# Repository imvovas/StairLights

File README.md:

# StairLights
Програмно-аппаратный комплект StairLights

Код для управления Arduino Leonardo (китайский клон)

В коде прошивки добавлены:
* управление скоростью отработки эффектов через подстроечный резистор;
* удалена поддержка кнопок вместе с библиотекой подавления дребезга;
* исправлены ошибки в визуальных эффектах.

Аппаратная часть находится в папке /Board. Актуальная версия платы в архиве StairLights_clips_2020-08-26.zip.
В актуальной редакции платы добавлены:
* дополнительные выводы 12 Вольт, 5 Вольт;
* добавлено два входа для сенсоров;
* добавлены отладочные светодиоды.
* Плата переведена на двухсторонний монтаж и под фабричное изготовление.

Ограничения:
- Напряжение питания устройства - 12 Вольт.
- Для питания Arduino Leonardo (китайский клон) использован DC-DC преобразователь (7-24 Вольта - 5 Вольт).
- Управляющие выходы подключаются к 8 сегментам LED-ленты 12 Вольт и потребляемой мощностью не более 500 мА на один сегмент.
- Используются управляющие сигналы TTL-уровня, при отсутствии сигнала входы притянуты к "земле".
- В качестве сенсоров можно использовать любые датчики/выключатели при условия соблюдения TTL-уровней сигнала. В коде прошивки реализована логика с поддержкой двух входов из четырех.

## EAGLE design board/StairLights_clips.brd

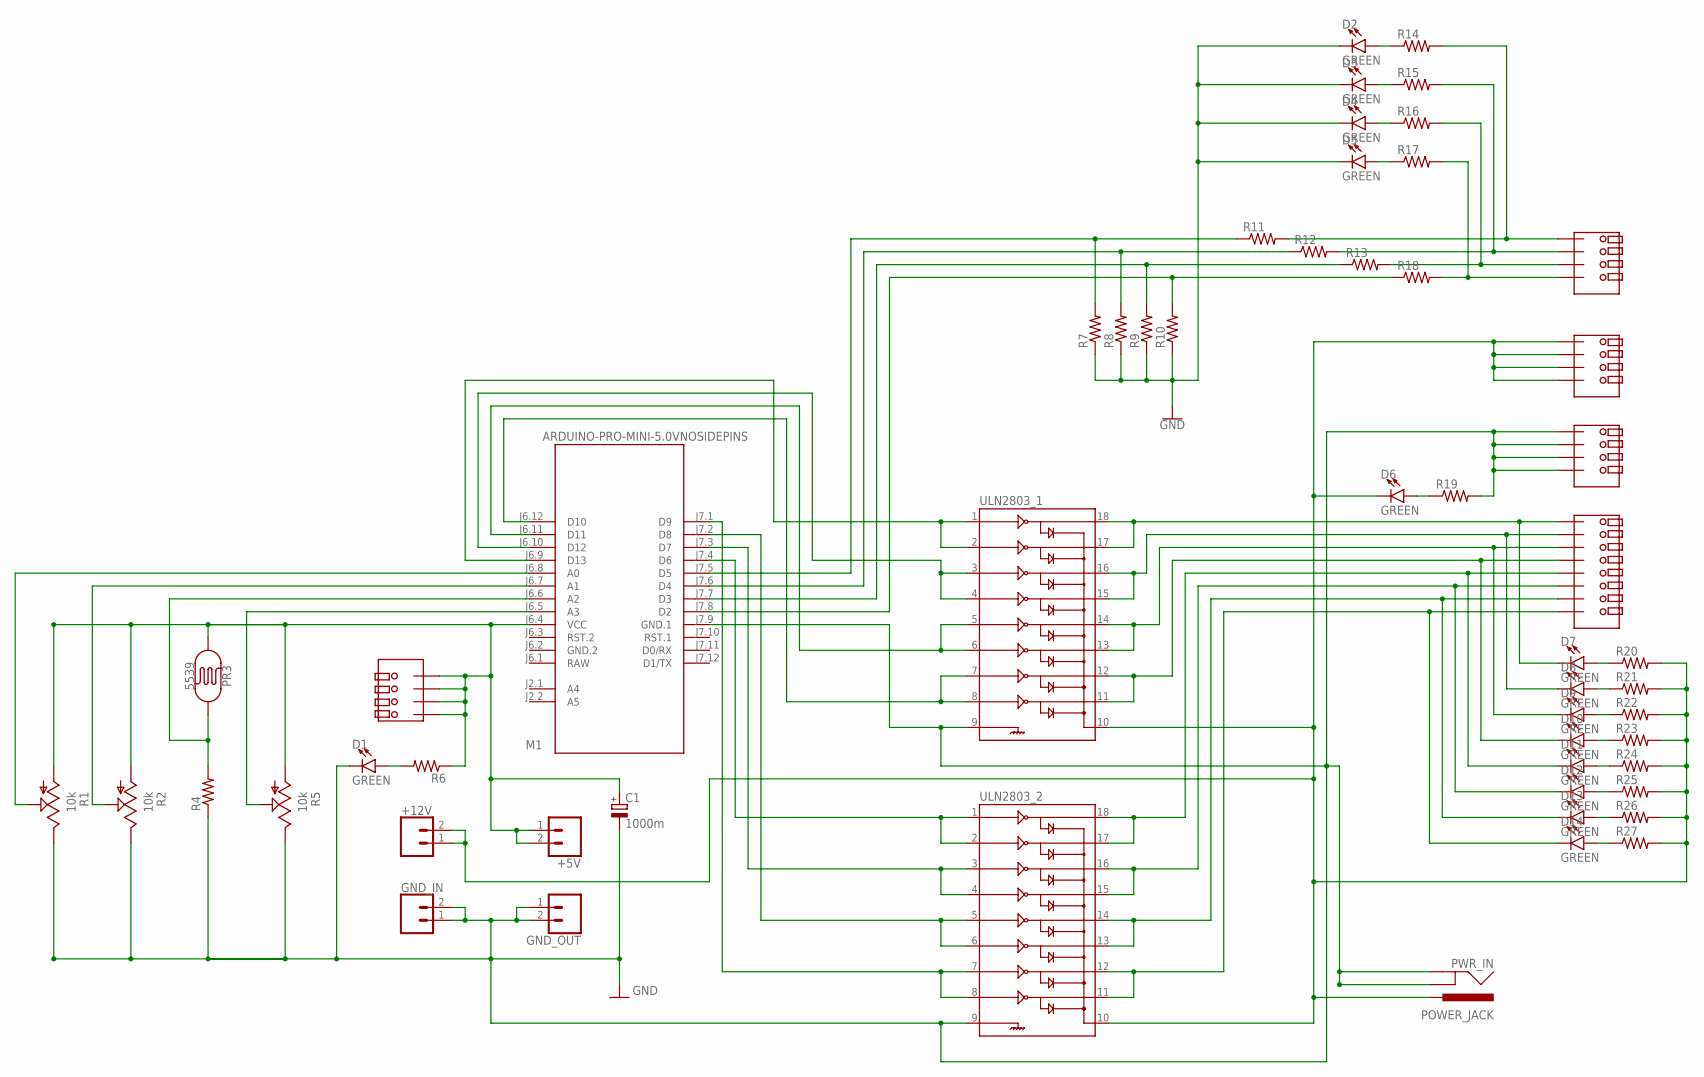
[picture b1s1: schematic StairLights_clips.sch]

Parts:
+5V, +12V: CONN_02; 1X02
C1: 1000m; E5-5
D1, D2, D3, D4, D5, D6, D7, D8, D9, D10, D11, D12, D13, D14: GREEN; LED-1206
GND_IN: CONN_02; 1X02
GND_OUT: CONN_02; 1X02
M1: ARDUINO-PRO-MINI-5.0VNOSIDEPINS; ARDUINO-PRO-MINI
PR3: 5539; PHOTOCELL
PWR_IN: POWER_JACK; POWER_JACK_PTH
R1, R2, R5: 10k; S64W
R4, R7, R8, R9, R10: 10k; R0805
R6, R11, R12, R13, R14, R15, R16, R17, R18, R19, R20, R21, R22, R23, R24, R25, R26, R27: 330; R0805
SC1, SC2, SC3, SC4: KF141V-4
SC5: KF141V-8
ULN2803_1, ULN2803_2: ULN2803DIP; DIL18

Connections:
GND: C1.-, D1.C, D2.C, D3.C, D4.C, D5.C, GND_IN.1, GND_IN.2, GND_OUT.1, GND_OUT.2, M1.J7.9 (GND.1), PWR_IN.GND, PWR_IN.GNDBREAK, R1.E, R2.E, R4.1, R5.E, R7.1, R8.1, R9.1, R10.1, R19.2, SC4.P$1, SC4.P$2, SC4.P$3, SC4.P$4, SC4.P$9, SC4.P$10, SC4.P$11, SC4.P$12, ULN2803_1.9, ULN2803_2.9
GND.2: M1.J6.2 (GND.2)
unnamed: D7.C, SC5.P$1, SC5.P$9, ULN2803_1.17, ULN2803_1.18
unnamed: D8.C, SC5.P$2, SC5.P$10, ULN2803_1.15, ULN2803_1.16
unnamed: M1.J7.7 (D3), R9.2, R13.1
unnamed: D9.C, SC5.P$3, SC5.P$11, ULN2803_1.13, ULN2803_1.14
unnamed: M1.J6.12 (D10), ULN2803_1.7, ULN2803_1.8
unnamed: D10.C, SC5.P$4, SC5.P$12, ULN2803_1.11, ULN2803_1.12
unnamed: M1.J6.6 (A2), PR3.2, R4.2
unnamed: D11.C, SC5.P$5, SC5.P$13, ULN2803_2.17, ULN2803_2.18
unnamed: D12.C, SC5.P$6, SC5.P$14, ULN2803_2.15, ULN2803_2.16
unnamed: M1.J6.11 (D11), ULN2803_1.5, ULN2803_1.6
unnamed: D13.C, SC5.P$7, SC5.P$15, ULN2803_2.13, ULN2803_2.14
unnamed: M1.J7.8 (D2), R10.2, R18.1
unnamed: M1.J7.3 (D7), ULN2803_2.3, ULN2803_2.4
unnamed: R13.2, R16.2, SC2.P$3, SC2.P$11
unnamed: M1.J6.5 (A3), R5.S
unnamed: D1.A, R6.2
unnamed: +5V.1, +5V.2, C1.+, M1.J6.4 (VCC), PR3.1, R1.A, R2.A, R5.A, R6.1, SC1.P$1, SC1.P$2, SC1.P$3, SC1.P$4, SC1.P$9, SC1.P$10, SC1.P$11, SC1.P$12
unnamed: D14.C, SC5.P$8, SC5.P$16, ULN2803_2.11, ULN2803_2.12
unnamed: R17.2, R18.2, SC2.P$4, SC2.P$12
unnamed: M1.J7.6 (D4), R8.2, R12.1
unnamed: M1.J7.1 (D9), ULN2803_2.7, ULN2803_2.8
unnamed: M1.J7.5 (D5), R7.2, R11.1
unnamed: R12.2, R15.2, SC2.P$2, SC2.P$10
unnamed: M1.J6.9 (D13), ULN2803_1.1, ULN2803_1.2
unnamed: R11.2, R14.2, SC2.P$1, SC2.P$9
unnamed: M1.J6.10 (D12), ULN2803_1.3, ULN2803_1.4
unnamed: M1.J6.7 (A1), R2.S
unnamed: M1.J6.8 (A0), R1.S
unnamed: M1.J7.4 (D6), ULN2803_2.1, ULN2803_2.2
unnamed: M1.J7.2 (D8), ULN2803_2.5, ULN2803_2.6
unnamed: D7.A, R20.1
unnamed: D8.A, R21.1
unnamed: D9.A, R22.1
unnamed: D10.A, R23.1
unnamed: D11.A, R24.1
unnamed: D12.A, R25.1
unnamed: D13.A, R26.1
unnamed: D14.A, R27.1
unnamed: +12V.1, +12V.2, D6.C, PWR_IN.PWR, R20.2, R21.2, R22.2, R23.2, R24.2, R25.2, R26.2, R27.2, SC3.P$1, SC3.P$2, SC3.P$3, SC3.P$4, SC3.P$9, SC3.P$10, SC3.P$11, SC3.P$12, ULN2803_1.10, ULN2803_2.10
unnamed: D6.A, R19.1
unnamed: D2.A, R14.1
unnamed: D3.A, R15.1
unnamed: D4.A, R16.1
unnamed: D5.A, R17.1
RAW: M1.J6.1 (RAW)

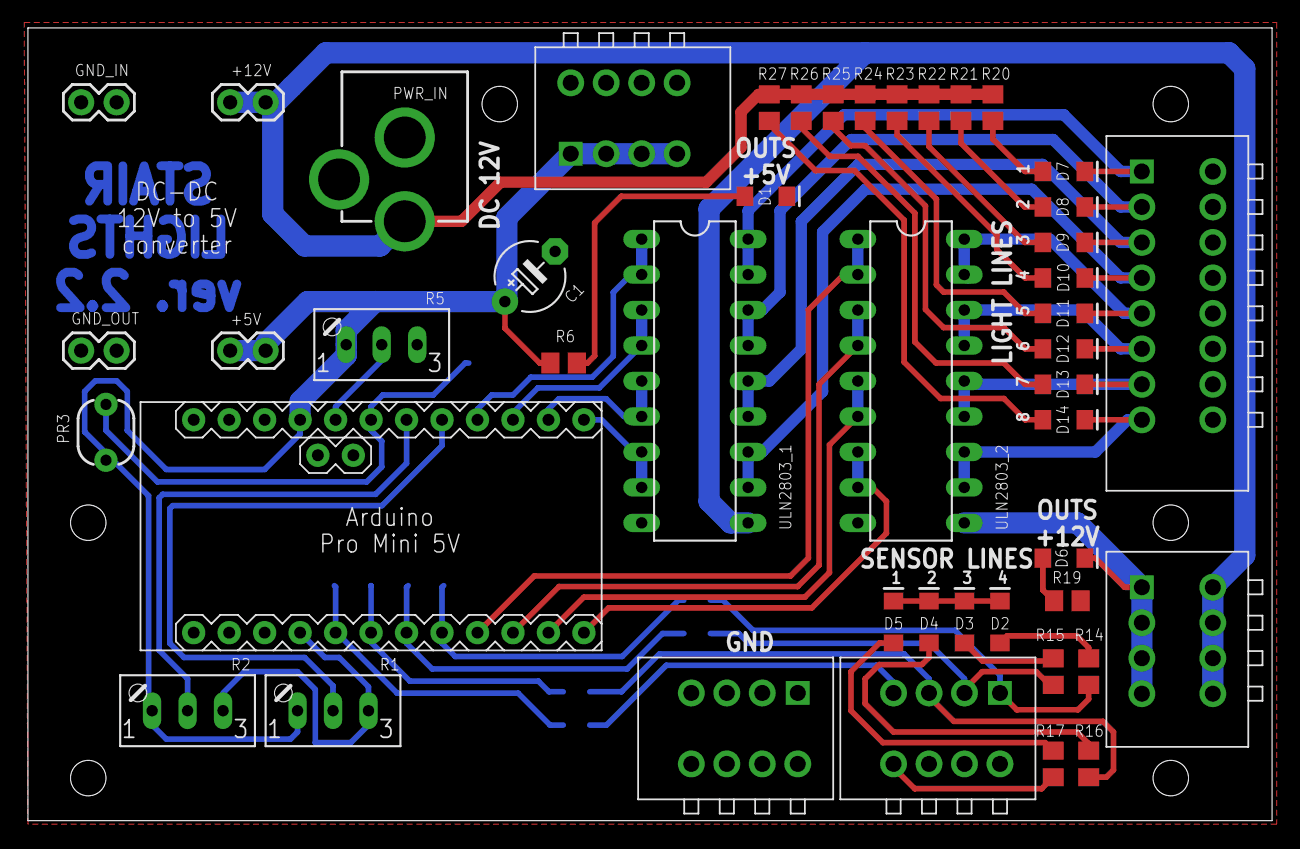
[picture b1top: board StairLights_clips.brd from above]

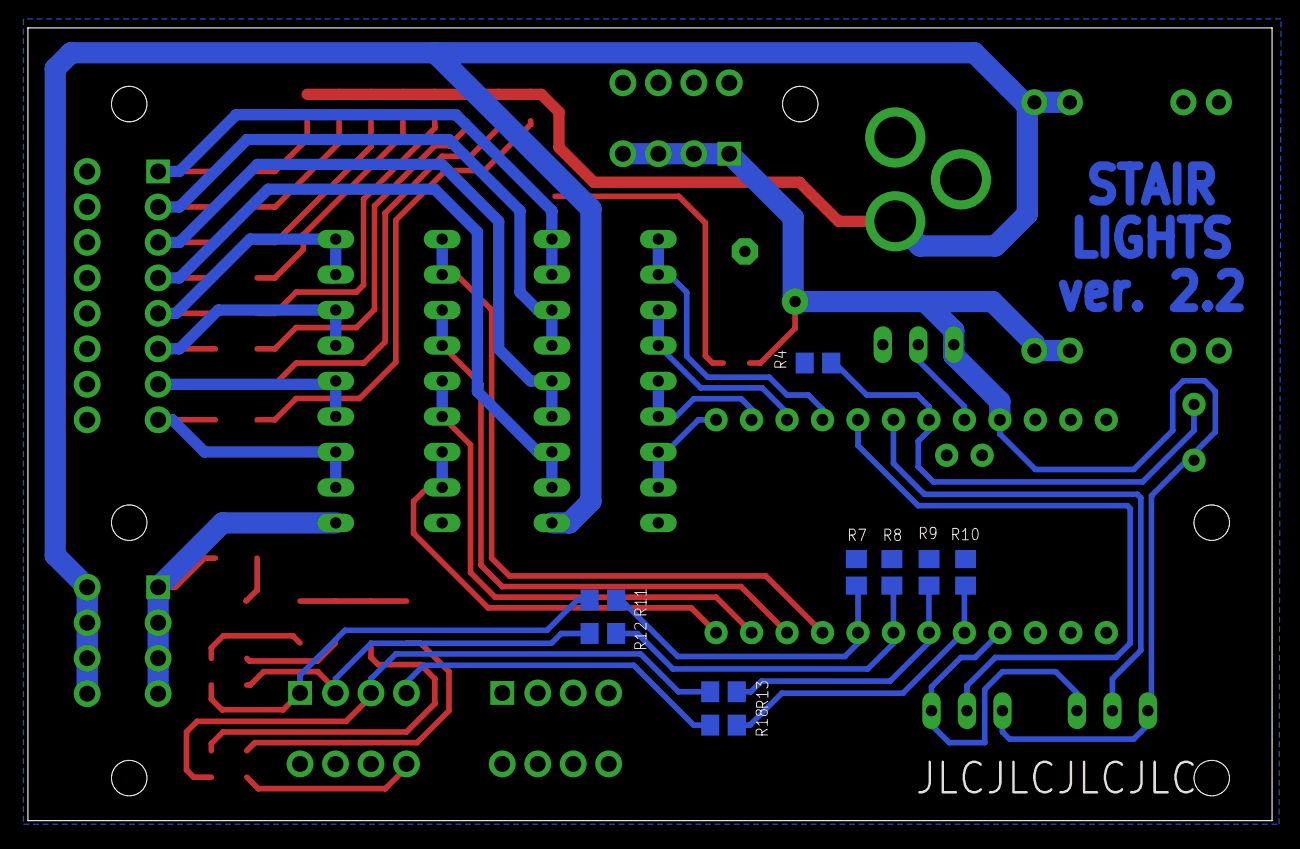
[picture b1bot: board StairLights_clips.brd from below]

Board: 2 copper layers, 89.1 x 56.8 mm, 55 parts (9 on the bottom side), 45 nets.

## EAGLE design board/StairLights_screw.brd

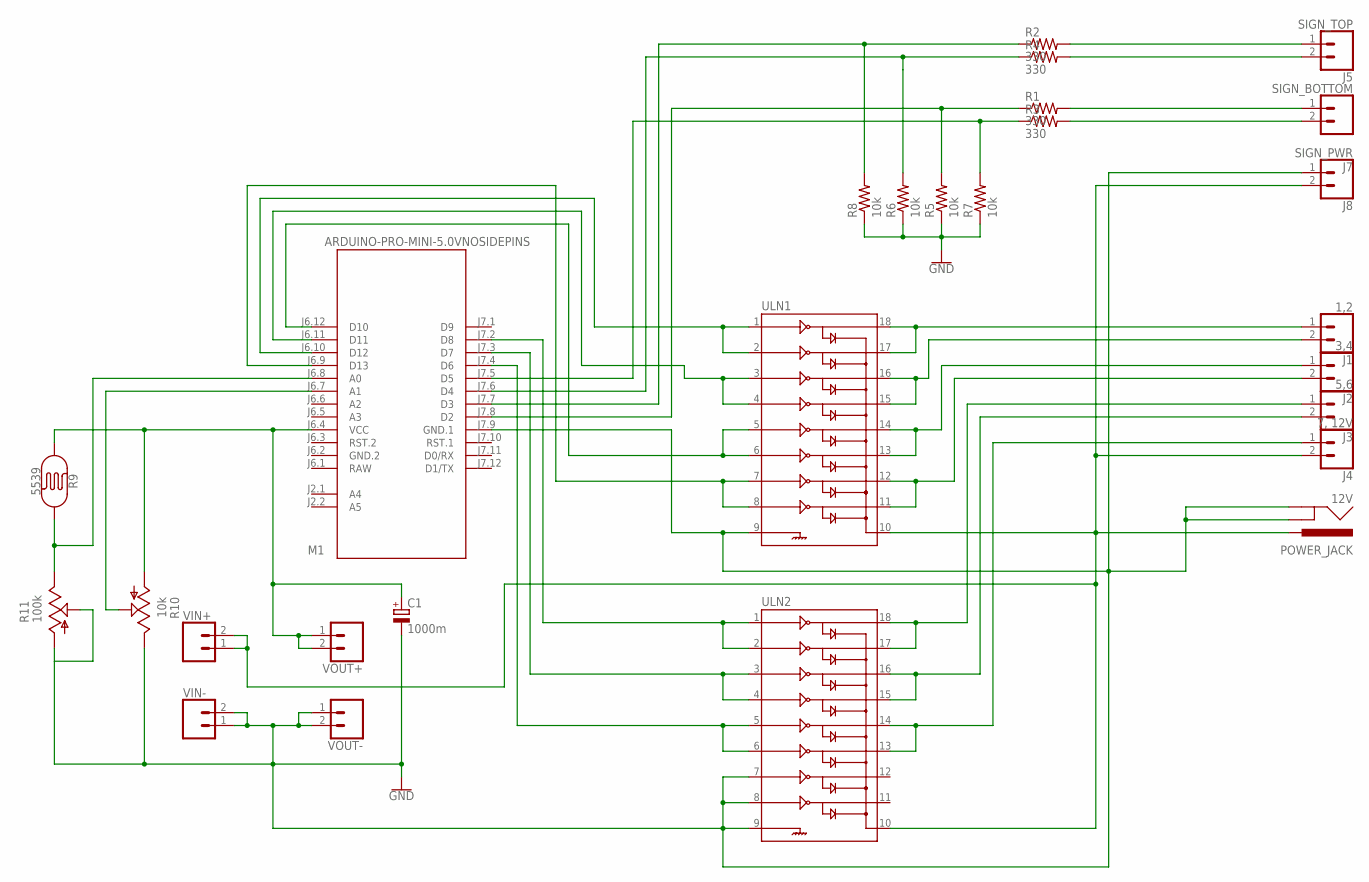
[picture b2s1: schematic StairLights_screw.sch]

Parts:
12V: POWER_JACK; POWER_JACK_PTH
C1: 1000m; E5-5
J1: 1,2; SCREWTERMINAL-5MM-2
J2: 3,4; SCREWTERMINAL-5MM-2
J3: 5,6; SCREWTERMINAL-5MM-2
J4: 7, 12V; SCREWTERMINAL-5MM-2
J5: SIGN_TOP; SCREWTERMINAL-5MM-2
J7: SIGN_BOTTOM; SCREWTERMINAL-5MM-2
J8: SIGN_PWR; SCREWTERMINAL-5MM-2
M1: ARDUINO-PRO-MINI-5.0VNOSIDEPINS; ARDUINO-PRO-MINI
R1, R2, R3, R4: 330; AXIAL-0.3
R5, R6, R7, R8: 10k; AXIAL-0.3
R9: 5539; PHOTOCELL
R10: 10k; S64W
R11: 100k; S64W
ULN1, ULN2: ULN2803DIP; DIL18
VIN+: CONN_02; 1X02
VIN-: CONN_02; 1X02
VOUT+: CONN_02; 1X02
VOUT-: CONN_02; 1X02

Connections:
GND: 12V.GND, 12V.GNDBREAK, C1.-, J8.1, M1.J7.9 (GND.1), R5.P$1 (1), R6.P$1 (1), R7.P$1 (1), R8.P$1 (1), R10.E, R11.A, R11.S, ULN1.9, ULN2.7, ULN2.8, ULN2.9, VIN-.1, VIN-.2, VOUT-.1, VOUT-.2
GND.2: M1.J6.2 (GND.2)
unnamed: J1.1, ULN1.17, ULN1.18
unnamed: J1.2, ULN1.15, ULN1.16
unnamed: M1.J7.7 (D3), R2.P$1 (1), R8.P$2 (2)
unnamed: J2.1, ULN1.13, ULN1.14
unnamed: M1.J6.12 (D10), ULN1.5, ULN1.6
unnamed: J2.2, ULN1.11, ULN1.12
unnamed: M1.J6.8 (A0), R9.2, R11.E
unnamed: J3.1, ULN2.17, ULN2.18
unnamed: J3.2, ULN2.15, ULN2.16
unnamed: M1.J6.10 (D12), ULN1.1, ULN1.2
unnamed: J4.1, ULN2.13, ULN2.14
unnamed: M1.J7.8 (D2), R1.P$1 (1), R5.P$2 (2)
unnamed: M1.J7.3 (D7), ULN2.3, ULN2.4
unnamed: M1.J7.4 (D6), ULN2.5, ULN2.6
unnamed: M1.J6.7 (A1), R10.S
unnamed: 12V.PWR, J4.2, J8.2, ULN1.10, ULN2.10, VIN+.1, VIN+.2
unnamed: C1.+, M1.J6.4 (VCC), R9.1, R10.A, VOUT+.1, VOUT+.2
unnamed: M1.J7.2 (D8), ULN2.1, ULN2.2
unnamed: M1.J7.6 (D4), R4.P$1 (1), R6.P$2 (2)
unnamed: M1.J7.5 (D5), R3.P$1 (1), R7.P$2 (2)
unnamed: J7.1, R1.P$2 (2)
unnamed: J7.2, R3.P$2 (2)
unnamed: M1.J6.9 (D13), ULN1.7, ULN1.8
unnamed: J5.2, R4.P$2 (2)
unnamed: J5.1, R2.P$2 (2)
unnamed: M1.J6.11 (D11), ULN1.3, ULN1.4
RAW: M1.J6.1 (RAW)

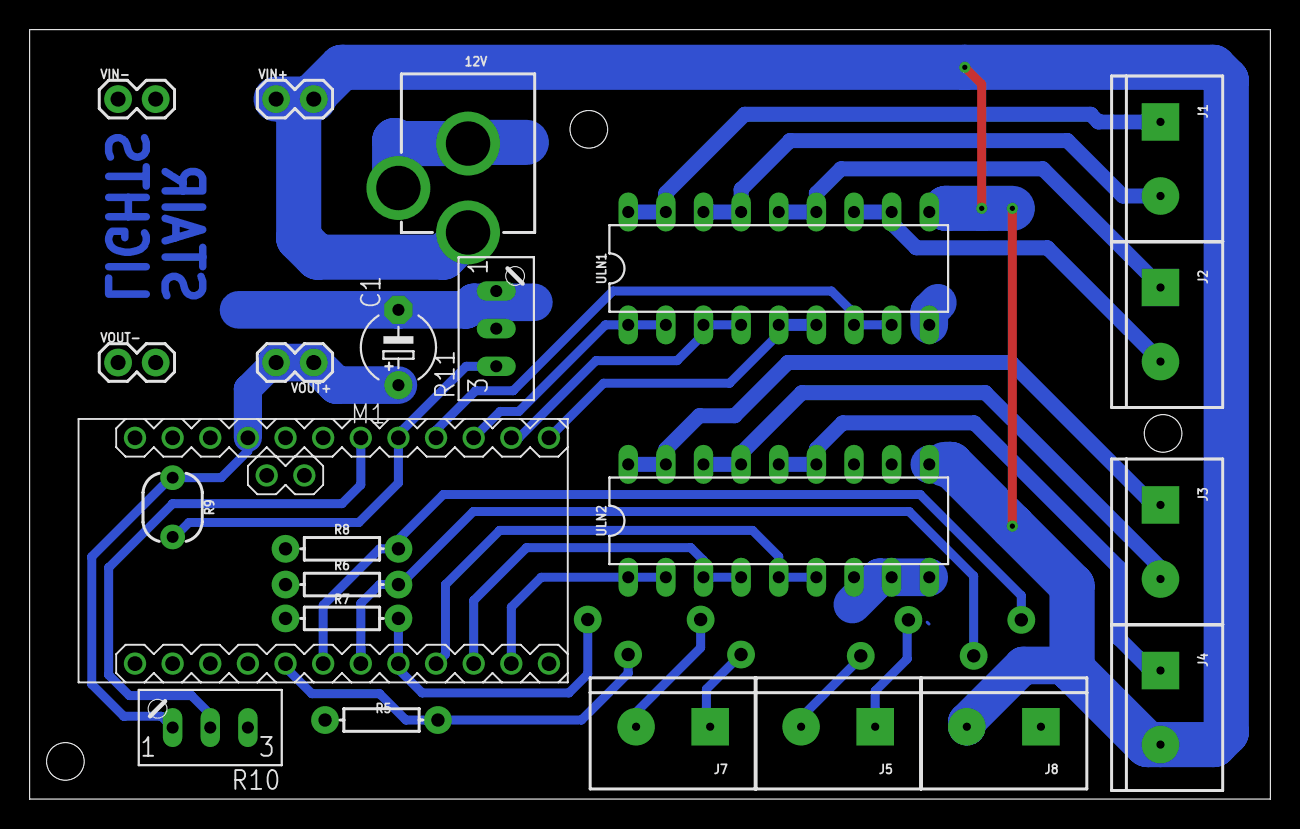
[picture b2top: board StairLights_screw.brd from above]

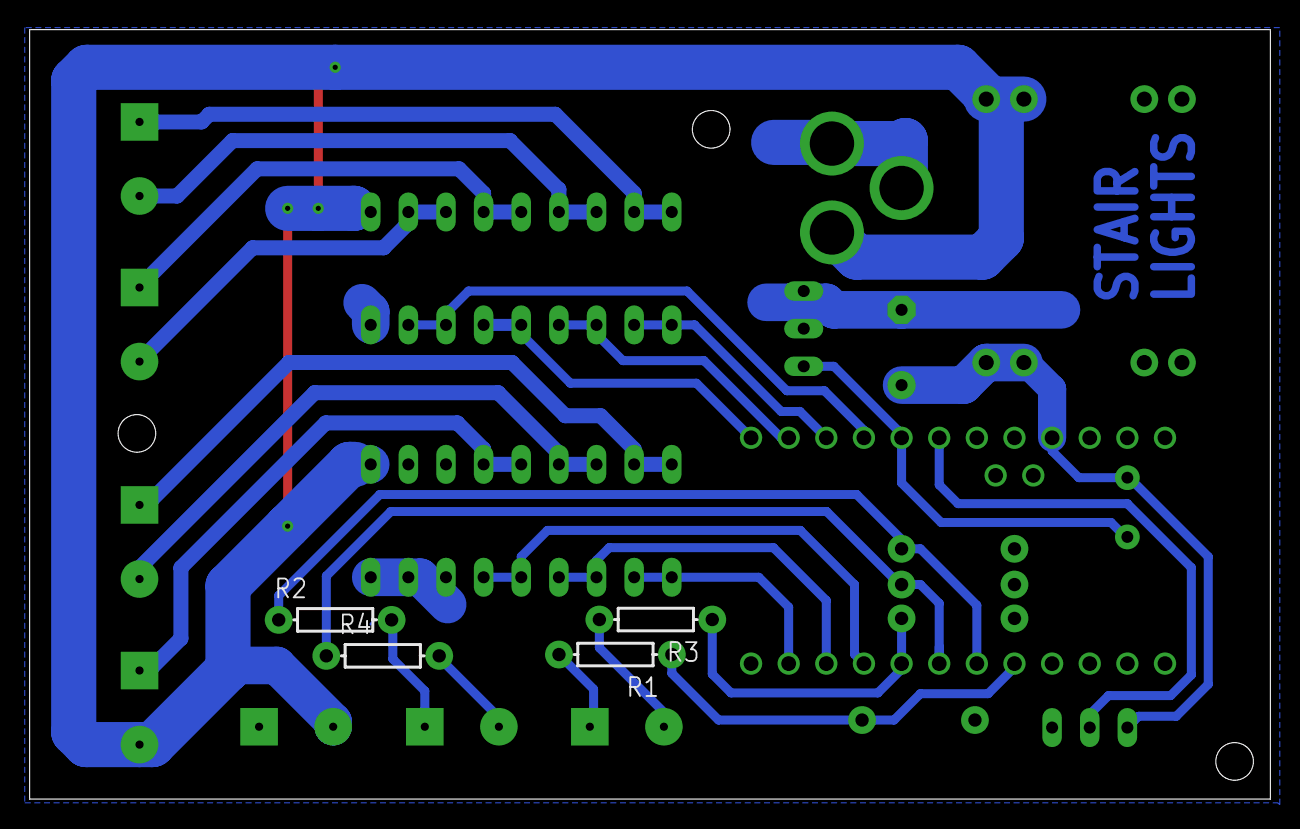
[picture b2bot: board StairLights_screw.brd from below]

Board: 2 copper layers, 83.7 x 51.9 mm, 27 parts (4 on the bottom side), 27 nets.

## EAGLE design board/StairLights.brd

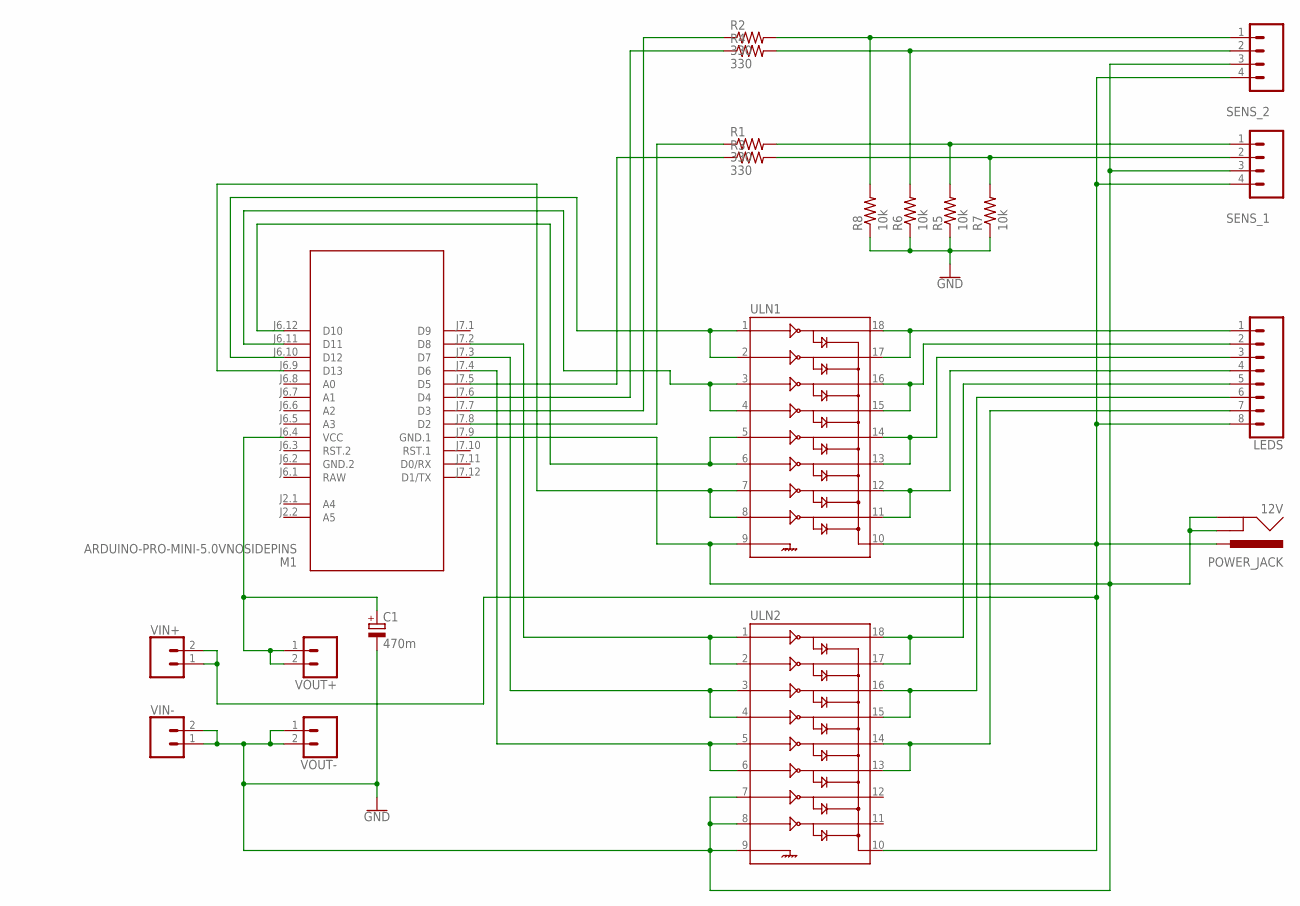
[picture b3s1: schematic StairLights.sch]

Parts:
12V: POWER_JACK; POWER_JACK_PTH
C1: 470m; E5-5
LEDS: CONN_08LONGPADS; 1X08_LONGPADS
M1: ARDUINO-PRO-MINI-5.0VNOSIDEPINS; ARDUINO-PRO-MINI
R1, R2, R3, R4: 330; AXIAL-0.3
R5, R6, R7, R8: 10k; AXIAL-0.3
SENS_1, SENS_2: CONN_04LONGPADS; 1X04_LONGPADS
ULN1, ULN2: ULN2803DIP; DIL18
VIN+: CONN_02; 1X02
VIN-: CONN_02; 1X02
VOUT+: CONN_02; 1X02
VOUT-: CONN_02; 1X02

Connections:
GND: 12V.GND, 12V.GNDBREAK, C1.-, M1.J7.9 (GND.1), R5.P$1 (1), R6.P$1 (1), R7.P$1 (1), R8.P$1 (1), SENS_1.3, SENS_2.3, ULN1.9, ULN2.7, ULN2.8, ULN2.9, VIN-.1, VIN-.2, VOUT-.1, VOUT-.2
GND.2: M1.J6.2 (GND.2)
unnamed: LEDS.1, ULN1.17, ULN1.18
unnamed: LEDS.2, ULN1.15, ULN1.16
unnamed: R2.P$2 (2), R8.P$2 (2), SENS_2.1
unnamed: LEDS.3, ULN1.13, ULN1.14
unnamed: M1.J6.12 (D10), ULN1.5, ULN1.6
unnamed: LEDS.4, ULN1.11, ULN1.12
unnamed: R4.P$2 (2), R6.P$2 (2), SENS_2.2
unnamed: LEDS.5, ULN2.17, ULN2.18
unnamed: LEDS.6, ULN2.15, ULN2.16
unnamed: M1.J6.10 (D12), ULN1.1, ULN1.2
unnamed: LEDS.7, ULN2.13, ULN2.14
unnamed: M1.J7.8 (D2), R1.P$1 (1)
unnamed: M1.J7.3 (D7), ULN2.3, ULN2.4
unnamed: M1.J7.4 (D6), ULN2.5, ULN2.6
unnamed: R1.P$2 (2), R5.P$2 (2), SENS_1.1
unnamed: 12V.PWR, LEDS.8, SENS_1.4, SENS_2.4, ULN1.10, ULN2.10, VIN+.1, VIN+.2
unnamed: C1.+, M1.J6.4 (VCC), VOUT+.1, VOUT+.2
unnamed: M1.J7.7 (D3), R2.P$1 (1)
unnamed: M1.J7.2 (D8), ULN2.1, ULN2.2
unnamed: M1.J7.6 (D4), R4.P$1 (1)
unnamed: R3.P$2 (2), R7.P$2 (2), SENS_1.2
unnamed: M1.J7.5 (D5), R3.P$1 (1)
unnamed: M1.J6.9 (D13), ULN1.7, ULN1.8
unnamed: M1.J6.11 (D11), ULN1.3, ULN1.4
RAW: M1.J6.1 (RAW)

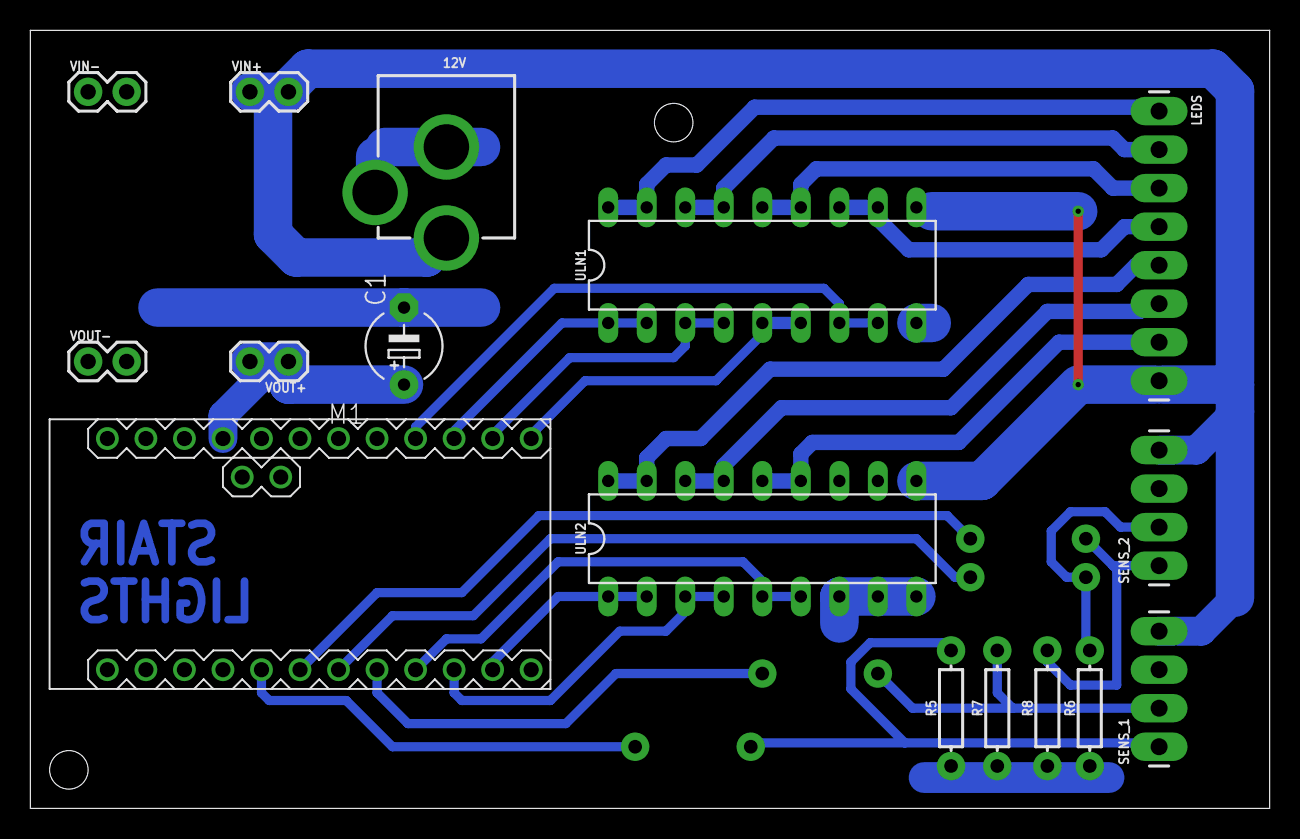
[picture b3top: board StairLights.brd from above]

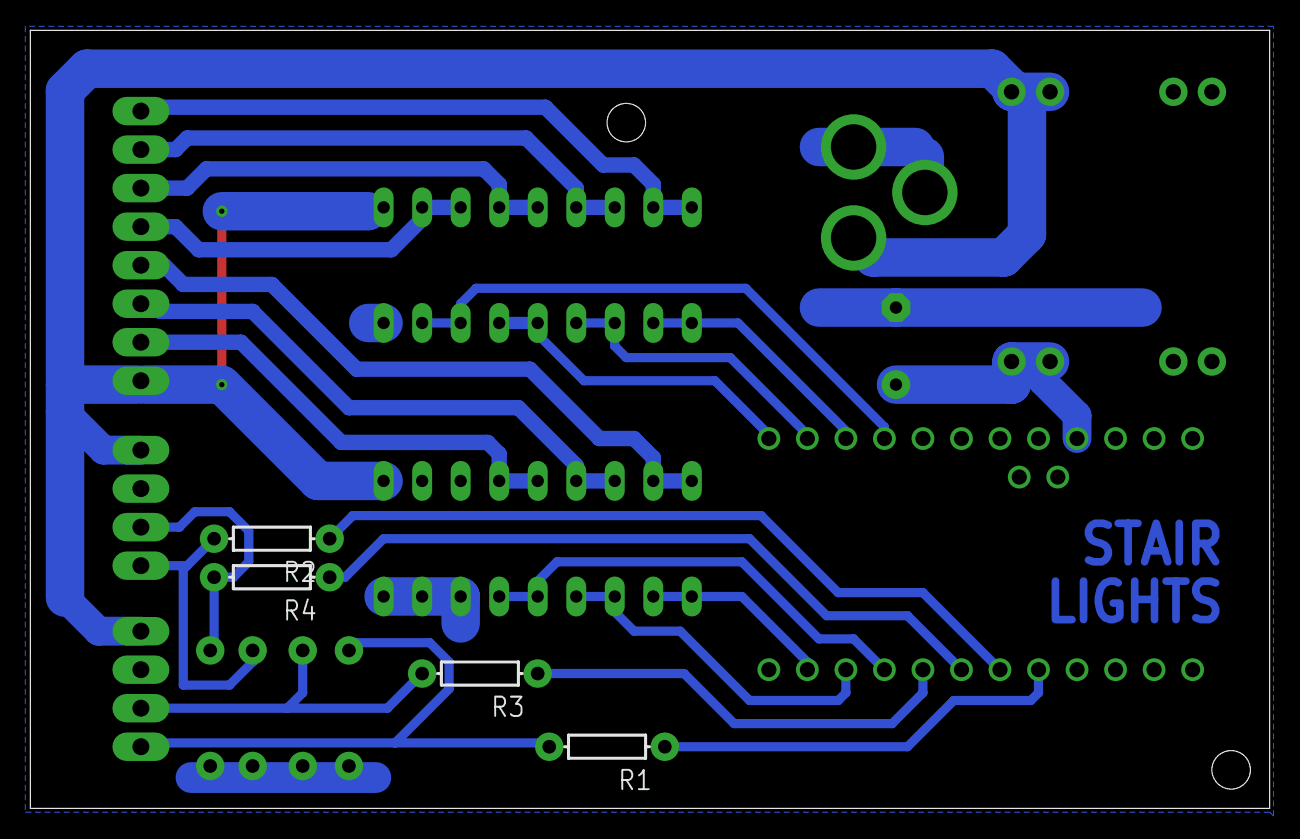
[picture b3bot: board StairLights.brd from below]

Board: 2 copper layers, 81.7 x 51.3 mm, 20 parts (4 on the bottom side), 25 nets.

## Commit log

2019-08-05 Уточнения
2019-08-05 Исправлена ошибка с номиналом потенциометра
2019-08-19 Update StairLights.ino
    Косметические правки в начальных настройках.
2020-08-26 Version 2020.08.26.001
    Исправление ошибок, переделка платы и т.п.
2020-08-27 Небольшие правки логики
2020-11-13 Some formatting

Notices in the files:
parts and their libraries:
SparkFun-Connectors: Licensing: Creative Commons ShareAlike 4.0 International - https://creativecommons.org/licenses/by-sa/4.0
diy-modules: Released under the Creative Commons Attribution 4.0 International License: http://creativecommons.org/licenses/by/4.0
